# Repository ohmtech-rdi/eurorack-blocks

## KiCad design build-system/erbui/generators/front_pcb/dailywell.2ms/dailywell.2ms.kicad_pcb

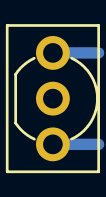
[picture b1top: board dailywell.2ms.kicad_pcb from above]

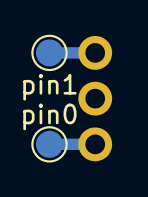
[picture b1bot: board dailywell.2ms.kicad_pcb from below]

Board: 2 copper layers, 3 parts (2 on the bottom side), 2 nets.

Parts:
Pin0, Pin1: TestPoint; TestPoint_Pad_D1.5mm
ZZ1: SW_SPDT; SW_SPDT_Dailywell

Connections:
unnamed: Pin0.1, ZZ1.1
unnamed: Pin1.1, ZZ1.3
